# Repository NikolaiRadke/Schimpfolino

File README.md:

### "Klappriger Blubberfetzen" "Nervendes Riesenungemach" "Windige Pupswindel"  
    
Who doesn't like to be insulted? Schimpfolino is an evil gadget that always has a saying ready. Small, handy, power saving. And completely useless. You need a PCB and some parts listed below. It's easy to build and long lasting for everyday use. Insert battery, press the button and recieve your daily insult!        

*Huch, Englisch? Kann ich nicht. Schnell [hier hin](https://github.com/NikolaiRadke/Schimpfolino/wiki)*.  

Schimpfolino is a random curse word generator with **12.288.000** possible combinations right now. That should be enough for a while. It's suitable for children (but still evil), maintenance-free and the battery lasts for years. And with the right case, it's an evil monster, like the **Nokolino shaped** case below! Just press the button, receive an insult, after eight seconds it turns off again. That's it. Evil. You can print the case in black! Black is an evil color. It is so evil. It is so evil that it hurts many people that are good!

What's new?  
* **12.04.2026** Updaed ATTinyCore URL.  
    -- More news? See the [newsblog](https://github.com/NikolaiRadke/Schimpfolino/tree/main/NEWS.md).   

### Notes for non-German Schimpfolino makers  
  
The building wiki and the curse words are in German. You need English words? **Contribute!**  

### Prerequisites

Except for the tools and some time, you need:
* Arduino IDE 1.6.6 or higher
* ATTinyCore from Spence Konde  
* Serial terminal software like *CuteCom* (Linux) or *CoolTerm* (Linux/Windows/Mac).  
* Arduino UNO/Nano/Whatever with USB cable
* A breadboard
* Some Dupont wires
* A 10 µF capacitor
* (Optional a 2 kOhm resistor)  
  
And the following hardware:
* Schimpfolino PCB 
* ATtiny25/45/85 (ATtiny25 for V1.4)
* 24AA64 or larger EEPROM (up to 24AA512) - with an ATtiny85, no EERPOM is needed (V1.5).
* 0,96" SDD1306 (V1.0) or 0,96"/1,3" SDD1306/SH1106 I2C display (V1.3)  
* Button 6 x 6 mm, 9,5 mm height
* 2 DIP-8 sockets
* Batteryholder, 20 mm pin spacing
* CR2032 battery
* Double-sided adhesive pad, 25 x 15 x 3 mm
* (Optional 2 100 nF capacitors)  
  
### Content

```
Schimpfolino/
Root directory with some explanation files.  
|
├── case/
|   STL files to 3D print a case. Other kinds of hulls will follow.
|   ├── Boring/
|   |   Plain but smooth case by Michael Kussmaul.
|   ├── CuteVader/
|   |   Cute and evil case by falsanu.
|   └── Nokolino/
|       Standard Nokolino-shaped case.
|
├── python/
|   Schimpfolino as python script.
|
├── schematics/
|   The circuit diagram, PCB renderings and gerber files.
|
└── src/
    Firmware and word files.
    ├── eeprom/
    |   All you need to flash your EEPROM.
    |   ├── eeprom_writer/
    |   |   Arduino sketch to write to your EEPROM.
    |   ├── files/
    |   |   The EEPROM content word lists and the editor.
    |   └── files_new/
    |       EEPROM content vor new version (1.4)
    |
    ├── Schimpfolino/
    |   Standard sketch with libraries used in the Make article. (1.0)
    ├── Schimpfolino_new/ (1.5)
    |   Version for new improvments. Compatible to old version.
    ├── Schimpfolino_nopeeprom/ (1.0)
    |   Sketch for Schimpfolino without EEPROM.
    └── Schimpfolino_nopeeprom_new/ (1.5)
        New version. Compatible to old version.
```

### Let's get started!

Ready? Great! Let's start here: [German wiki](https://github.com/NikolaiRadke/Schimpfolino/wiki).  

## 💙 Support Schimpfolino

Schimpfolino is free and open source. If he saved your day, consider buying me a coffee! ☕

Every contribution helps keep this project alive! 🚀

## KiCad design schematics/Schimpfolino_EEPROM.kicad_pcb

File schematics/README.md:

# Schematics

In this folder you can find the circuit diagram **Schimpfolino.pdf**, the PCB renderings and the gerber files to print your PCBs, with the unusual name **gerber.zip**. Upload the file to the PCB dealer of your choice or the dealer you trust and build your own Schimpfolino. Don't hesitate!

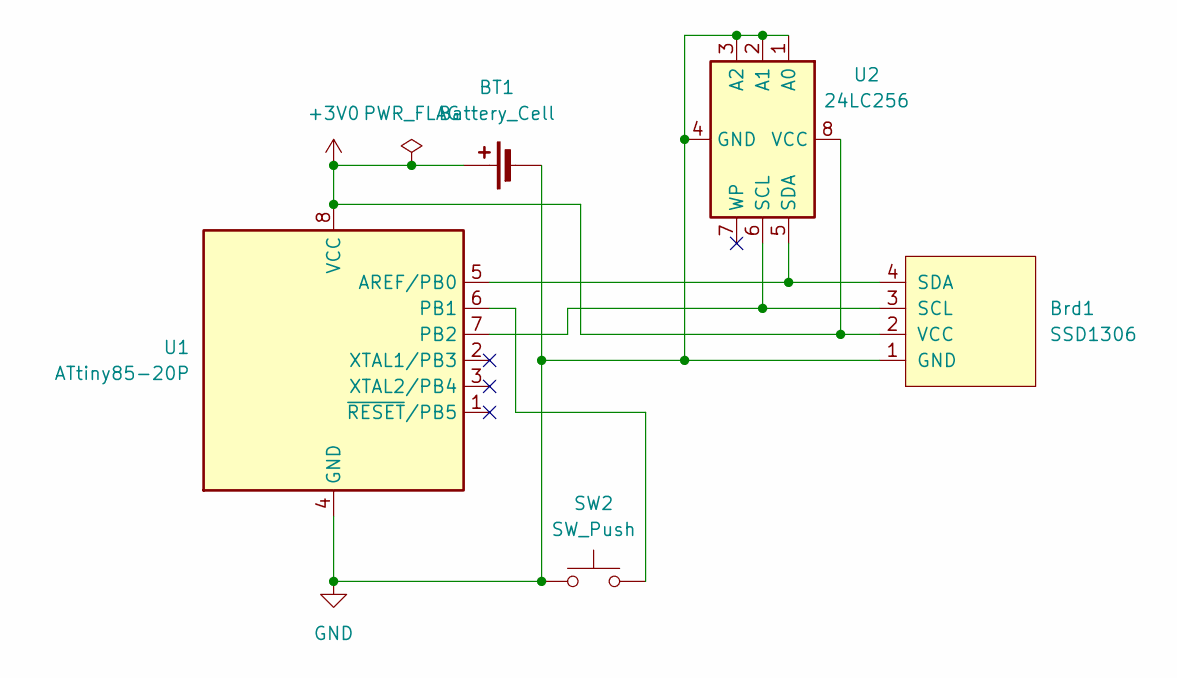
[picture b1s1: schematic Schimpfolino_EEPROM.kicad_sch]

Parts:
BT1: Battery_Cell; Battery_Panasonic_CR2032-HFN_Horizontal_CircularHoles
Brd1: SSD1306; 128x64OLED
SW2: SW_Push; SW_PUSH_6mm
U1: ATtiny85-20P; DIP787W46P254L927H533Q8
U2: 24LC256; DIP787W46P254L927H533Q8

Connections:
+3V0: BT1.1 (+), Brd1.2 (VCC), U1.8 (VCC), U2.8 (VCC)
GND: BT1.2 (-), Brd1.1 (GND), SW2.1, U1.4 (GND), U2.1 (A0), U2.2 (A1), U2.3 (A2), U2.4 (GND)
unnamed: Brd1.3 (SCL), U1.7 (PB2), U2.6 (SCL)
unnamed: Brd1.4 (SDA), U1.5 (AREF/PB0), U2.5 (SDA)
unnamed: SW2.2, U1.6 (PB1)

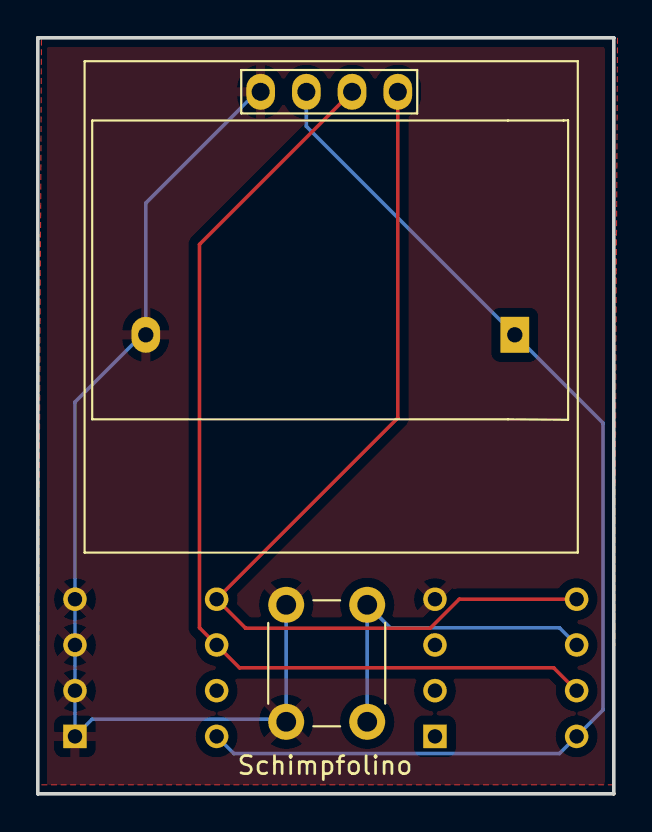
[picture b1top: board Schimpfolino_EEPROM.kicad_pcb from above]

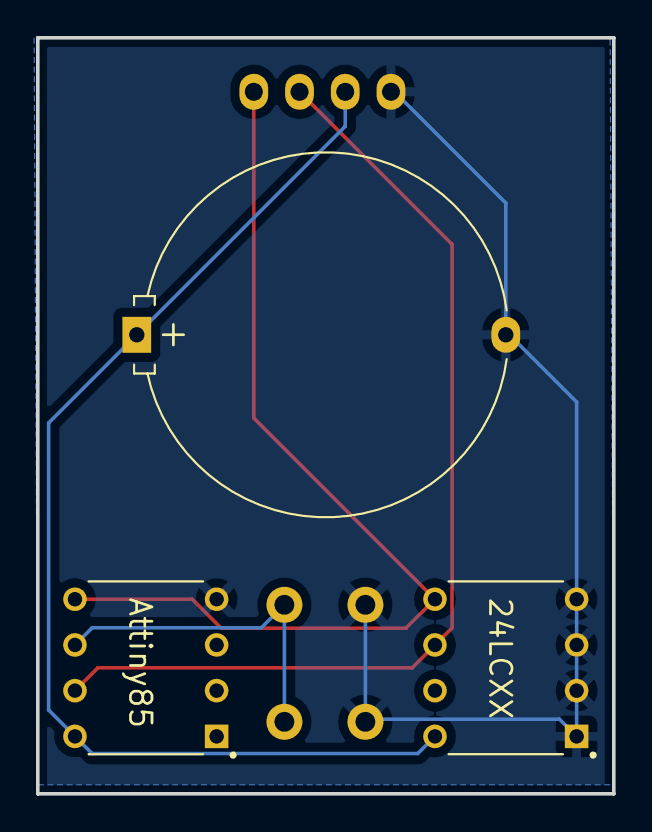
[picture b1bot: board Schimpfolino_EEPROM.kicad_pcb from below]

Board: 2 copper layers, 32.0 x 42.0 mm, 5 parts (3 on the bottom side), 5 nets.

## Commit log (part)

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2024-07-11 Halfed idle power draw
2024-07-13 Code cleanup
2024-07-13 Reworked power management V1.0-130724
2024-07-27 Corrected SDA in sketch wiring diagram
2024-07-31 Changed gender variable name to genus. Be modern, Schimpfolino!
2024-08-01 Corrected some comments
2024-08-05 Added some comments
2024-08-07 New board and V1.0 release!
2024-08-10 Added code of conduct
2024-08-10 Each line of code now has a comment!
2024-08-20 Small code cleanup
2024-08-25 Switched to 24AAXXX EEPROM
2024-08-26 Code comments cleanup
2024-08-29 Slighty flash usage improvments V1.0-290824
2024-09-05 Big Umlaute are supportet. 1.0-050924
2024-09-08 Slightly improved word list editor
2024-09-08 Added some comments to eeprom_writer
2024-09-10 Cleanup code
2024-09-13 eeprom_writer is a bit mir talkative.
2024-09-19 Spelling corrections
2024-09-26 Fixed a typo in eeprom5.txt
2024-09-30 Removed birne from male list
2024-10-01 One more typo fixed.
2024-10-10 New V1.01 version for new improvments
2024-10-10 Cleanup
2024-10-11 Found a small error in the comments
2024-10-11 Better helping variable handling
2024-10-12 Spelling corrections in comments
2024-10-15 Polished comments
2024-10-16 Corrections and workaround for Schimpfolino_noeeprom.ino
2024-10-17 Better word editor mobile layout
2024-10-17 New V1.01 versions are not working correct
2024-10-18 1.01-181024 is working now.
2024-10-19 Aktualisieren von README.md
2024-10-19 Aktualisieren von NEWS.md
2024-10-19 Fixed the noeeprom-bug and removed the workaround
2024-10-21 1.02-211024
2024-10-22 Comments clean up in the new versions
2024-10-26 Added support for SH1106 displays
2024-10-27 Library cleanup
2024-10-27 V1.1-27102024 with easy SH1106 support.
2024-10-29 V1.2 with new optional bold font
2024-10-29 V1.2-29102024 for V1.2 release
2024-10-30 1.2-30102024. Shrunk libraries
2024-11-05 Fixed bad text centering
2024-11-05 Auto count words in lists
2024-11-06 Removed useless function in oled library
2024-11-07 Wordlist for _noeeprmom is now an external file
2024-12-20 Update oled.cpp
    Fixed glitch in character ü
2024-12-24 Increased OLED init time for more compatiblity
2024-12-28 New 'boring' case
2025-01-16 Version V1.22 and V1.01 with final centering :-)
2025-02-20 Updated eeprom_writer
2025-03-13 Fix for long words and V1.3 full 1,3'' support
2025-03-14 Spelling corrections in the comments
2025-03-20 added 3dmodel
2025-03-20 New Cute Vader case
2025-04-07 Firmware 1.X-070425 with code optimizations
2025-04-15 V1.x-150425
2025-05-03 V1.X 03052025 with 86 bytes less
2025-05-08 New V1.4-07052025 with more flash saving
2025-05-08 Fixed small bug with bold font ä
2025-05-15 Firmware 1.X-150525
2025-07-26 Schimpfolino.py
2025-08-05 some typos
2025-08-06 refactored o/src/eeprom/files_new/eeprom.html with 5 paralell containers
2026-01-07 Release V1.5
2026-01-07 Update NEWS.md with v1.5 release details
    Added release notes for version 1.5 including improvements.
2026-01-07 Clarify Schimpfolino_noeeprom_new description
    Updated description of Schimpfolino_noeeprom_new to clarify it includes a complete compressed internal word list.
2026-01-07 Refine wording in TODO.md for completed tasks
    Corrected phrasing for clarity in the Done section of TODO.md.
2026-04-12 Update release date and ATTinyCore URL
    Updated the release date and corrected the ATTinyCore URL in the README.
2026-04-12 Fix typo in ATTinyCore URL update entry
2026-04-13 Add ATTinyCore requirement to README
